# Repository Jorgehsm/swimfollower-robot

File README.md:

Projeto e Implementação de um Robô com Sistema de Rastreamento para Monitoramento de Nadadores

Este repositório contém o código-fonte e os arquivos de projeto desenvolvidos para o Trabalho de Conclusão de Curso em Engenharia Mecatrônica na Universidade Federal de Uberlândia. O projeto consiste em um robô móvel autônomo projetado para acompanhar nadadores de alto desempenho em tempo real, automatizando a coleta de métricas biomecânicas.
Visão Geral

O sistema utiliza processamento de visão computacional embarcado para detectar alvos e um sistema de controle em malha fechada para ajustar a velocidade dos motores, mantendo o nadador centralizado no campo de visão da câmera.
Componentes Principais

    Processamento de Visão: Raspberry Pi 4 (8 GB RAM) executando modelos YOLOv8n.

    Controle de Baixo Nível: Microcontrolador ESP32 para controle PWM dos motores e leitura de encoders.

    Atuadores: Motores CC JGY-370

    Estrutura: Chassi fabricado em impressão 3D (PLA/ABS) e perfis de alumínio.

    Interface: Webserver baseado em Flask para operação remota e monitoramento.

Arquitetura de Software

O software está dividido em scripts principais que gerenciam desde a coleta de dados até a inferência final:

    dataSampling.py: Interface para captura de frames e criação de datasets rotulados.

    model.py: Utilizado para ensaios de resposta ao degrau e identificação do modelo físico da planta.

    inference.py: Script de operação final que executa a rede neural e a malha de controle PID.

    Firmware ESP32: Gerencia o algoritmo PID, funções anti-windup e a comunicação serial com o Raspberry Pi.

Como Utilizar
Requisitos de Conexão

O acesso ao sistema embarcado é feito via protocolo SSH: ssh user@[IP_DO_ROBO]

Execução via Scripts Shell

Foram criados scripts facilitadores para iniciar as diferentes etapas do projeto:

    Para coleta de dados: ./run_data.sh

    Para modelagem do sistema: ./run_model.sh

    Para operação em malha fechada: ./run_inference.sh 

Transferência de Arquivos

Para baixar vídeos, logs em .csv ou imagens geradas, utilize o comando SCP:
Bash

scp -r user@[IP_DO_ROBO]:/home/user/swimfollower-robot/[PATH] [DESTINO_LOCAL]

Modelo de Controle

A planta foi identificada como um sistema integrador com ganho estático médio Kmedio ​= 1,011. O controlador PID projetado utiliza os seguintes ganhos para garantir um regime superamortecido (ξ=1,42) e evitar oscilações na filmagem:

    Kp: 2,0

    Ki: 0,4

    Kd: 0,25

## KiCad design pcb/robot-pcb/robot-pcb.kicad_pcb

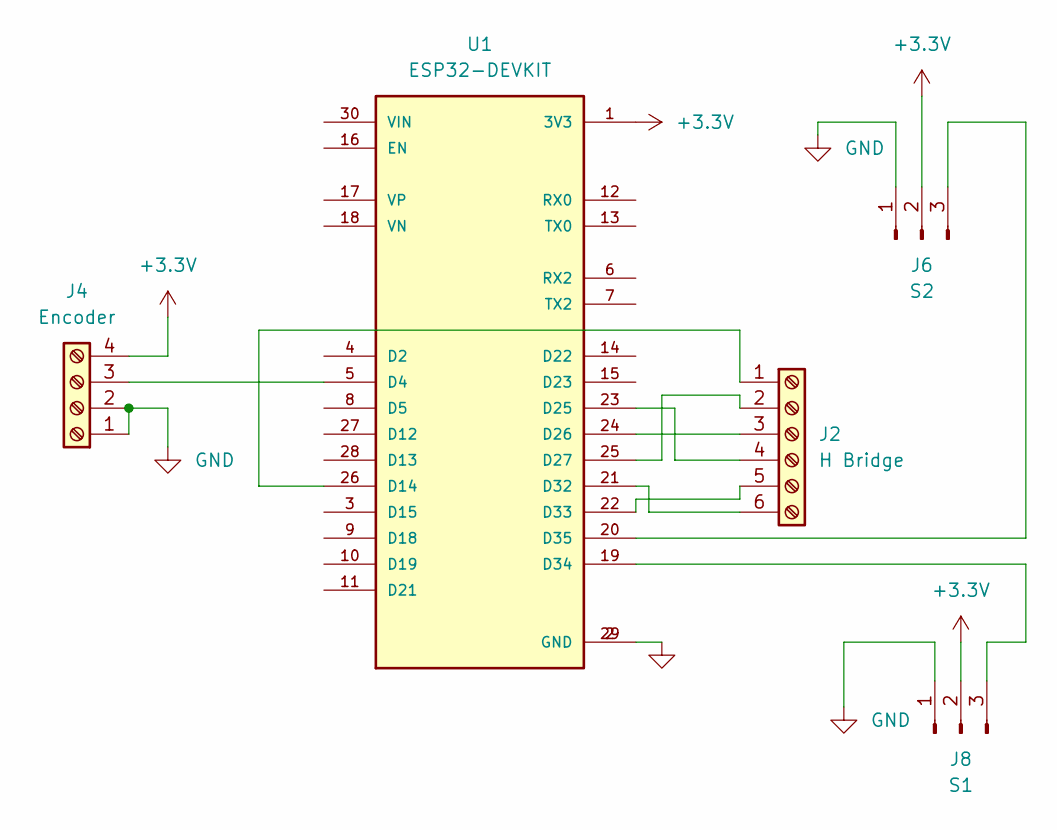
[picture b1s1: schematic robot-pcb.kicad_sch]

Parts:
J2: H Bridge; TerminalBlock_bornier-6_P5.08mm
J4: Encoder; TerminalBlock_bornier-4_P5.08mm
J6: S2; PinHeader_1x03_P2.54mm_Vertical
J8: S1; PinHeader_1x03_P2.54mm_Vertical
U1: ESP32-DEVKIT; MODULE_ESP32_DEVKIT_V1; PARTREV N/A

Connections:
+3.3V: J4.4, J6.2, J8.2, U1.1 (3V3)
GND: J4.1, J4.2, J6.1, J8.1, U1.2 (GND), U1.29 (GND)
unnamed: J2.1, U1.26 (D14)
unnamed: J2.2, U1.25 (D27)
unnamed: J2.3, U1.24 (D26)
unnamed: J2.4, U1.23 (D25)
unnamed: J2.5, U1.22 (D33)
unnamed: J2.6, U1.21 (D32)
unnamed: J4.3, U1.5 (D4)
unnamed: J6.3, U1.20 (D35)
unnamed: J8.3, U1.19 (D34)

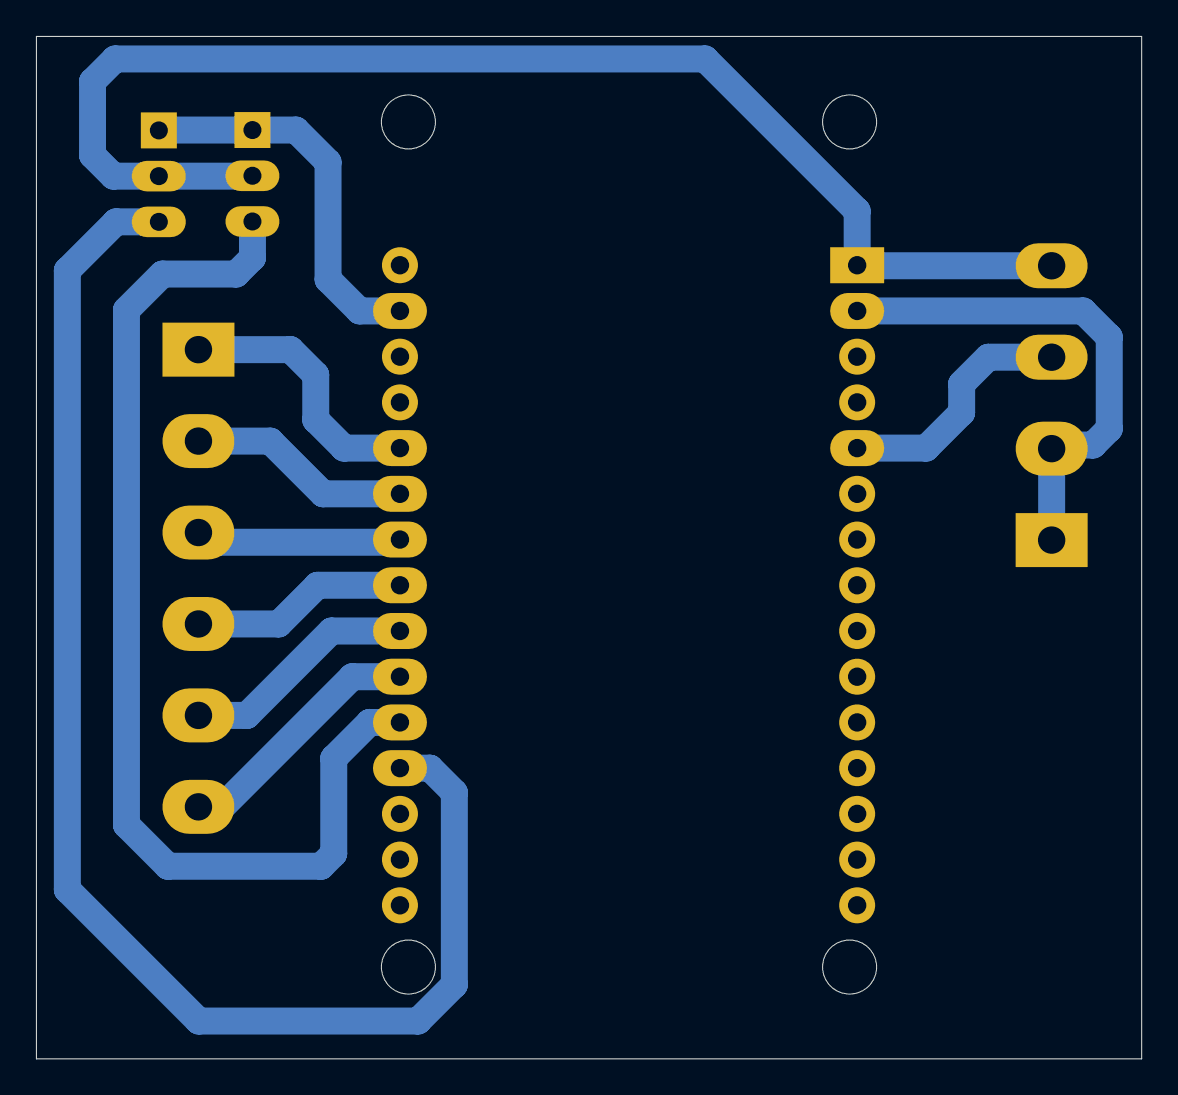
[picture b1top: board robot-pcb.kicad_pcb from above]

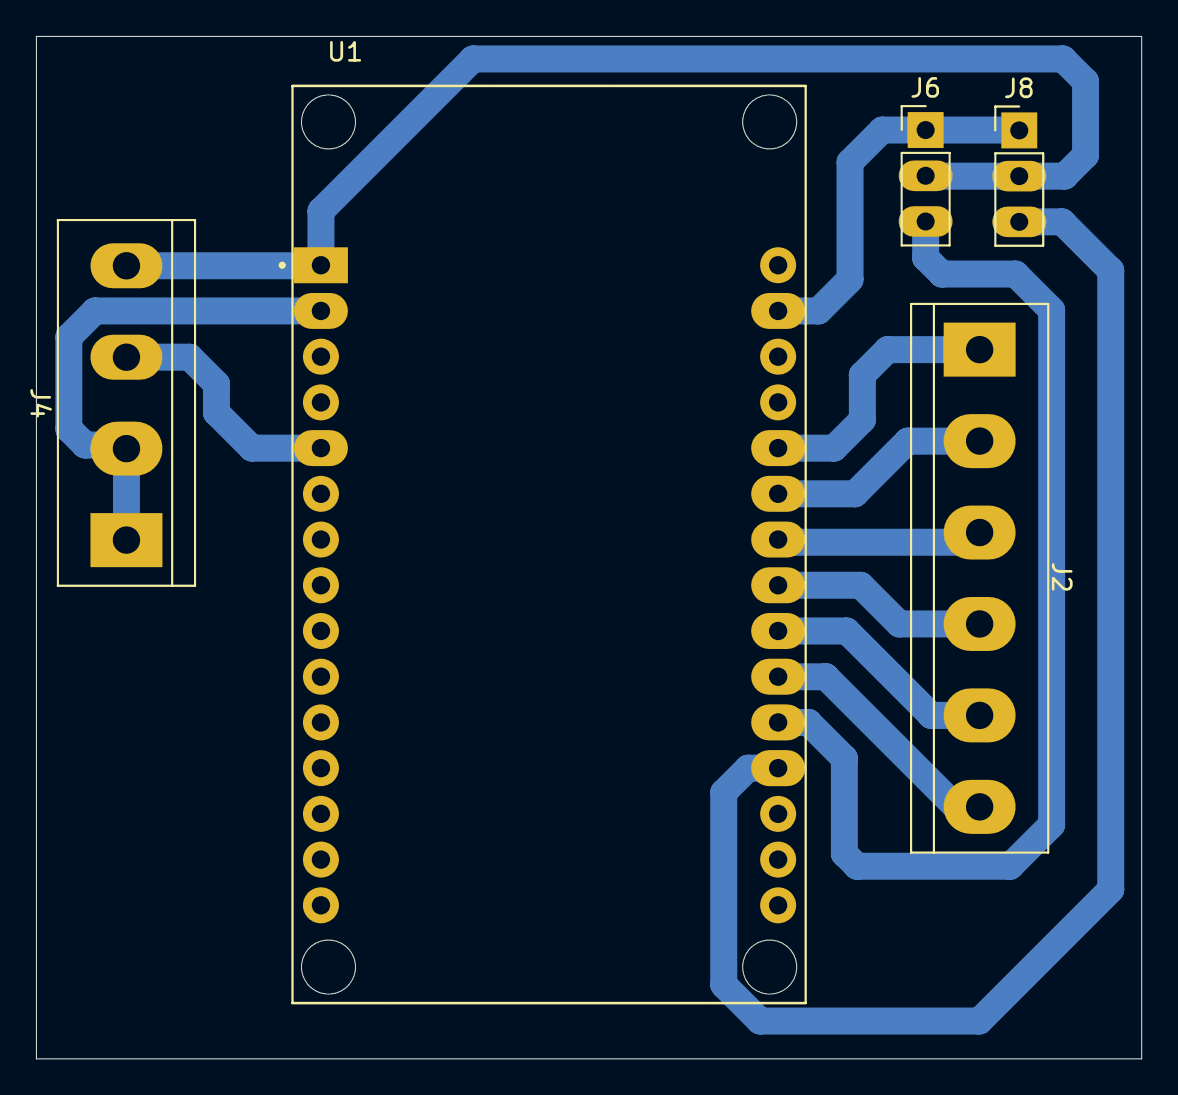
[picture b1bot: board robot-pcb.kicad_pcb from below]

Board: 2 copper layers, 61.4 x 56.8 mm, 5 parts (5 on the bottom side), 11 nets.

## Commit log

2025-07-10 create esp32 firmware
2025-07-12 Setting right pins and creating pcb model
2025-07-13 Testing imagem detection with yolo8n-face and communication with microcontroller
2025-07-23 Commiting last image detection test
2025-07-28 requirements raspberry
2025-08-02 Motor speed test varying duty cylce
2025-08-02 Testing camera on linux
2025-08-02 Testing inference on rpi
2025-08-05 Testing motor and encoder
2025-08-10 Battery connection scheme
2025-08-10 Mais testes com motor
2025-08-22 Updating control firmware
2025-08-23 testing labelling and training a model with swimmers video
2025-09-20 Live feed testing
2025-09-20 recording while doing inference
2025-09-21 implementing web server for colleting training data
2025-09-27 Initial tests with data collection
2025-10-05 Testing data collection on embedded
2025-10-15 Altering dataset collection to capturing images instead of video
2025-10-19 Obstacle sensor test
2025-10-25 Testing data collection and open loop control
2025-10-25 Testing inference web server on desktop
2025-10-31 control logic changes
2025-11-01 Adjusting gains through web server
2025-11-01 Testing control firmware on robot
2025-11-02 Fixing segmentation fault and sending serial flag when closing
2025-11-03 Scripts for QoL
2025-11-04 Python script for capturing system model, improving QoL scripts and file structure, fixing seg fault and other bugs in interfaceWebControl
2025-11-18 Solving segfault and renaming folders
2026-01-11 Testing model exported as NCNN
2026-01-11 Fixing video recorder speed
2026-01-11 Fixing which script to use
2026-01-12 Acquiring offset data for modelling
2026-01-15 Generating graphs and getting model
2026-01-15 Adding csv for offset during closed loop operation
2026-01-15 Adding deadzone to controller
2026-01-15 Fixing controller
2026-01-29 Final version
2026-01-29 Update README with project details and usage instructions
